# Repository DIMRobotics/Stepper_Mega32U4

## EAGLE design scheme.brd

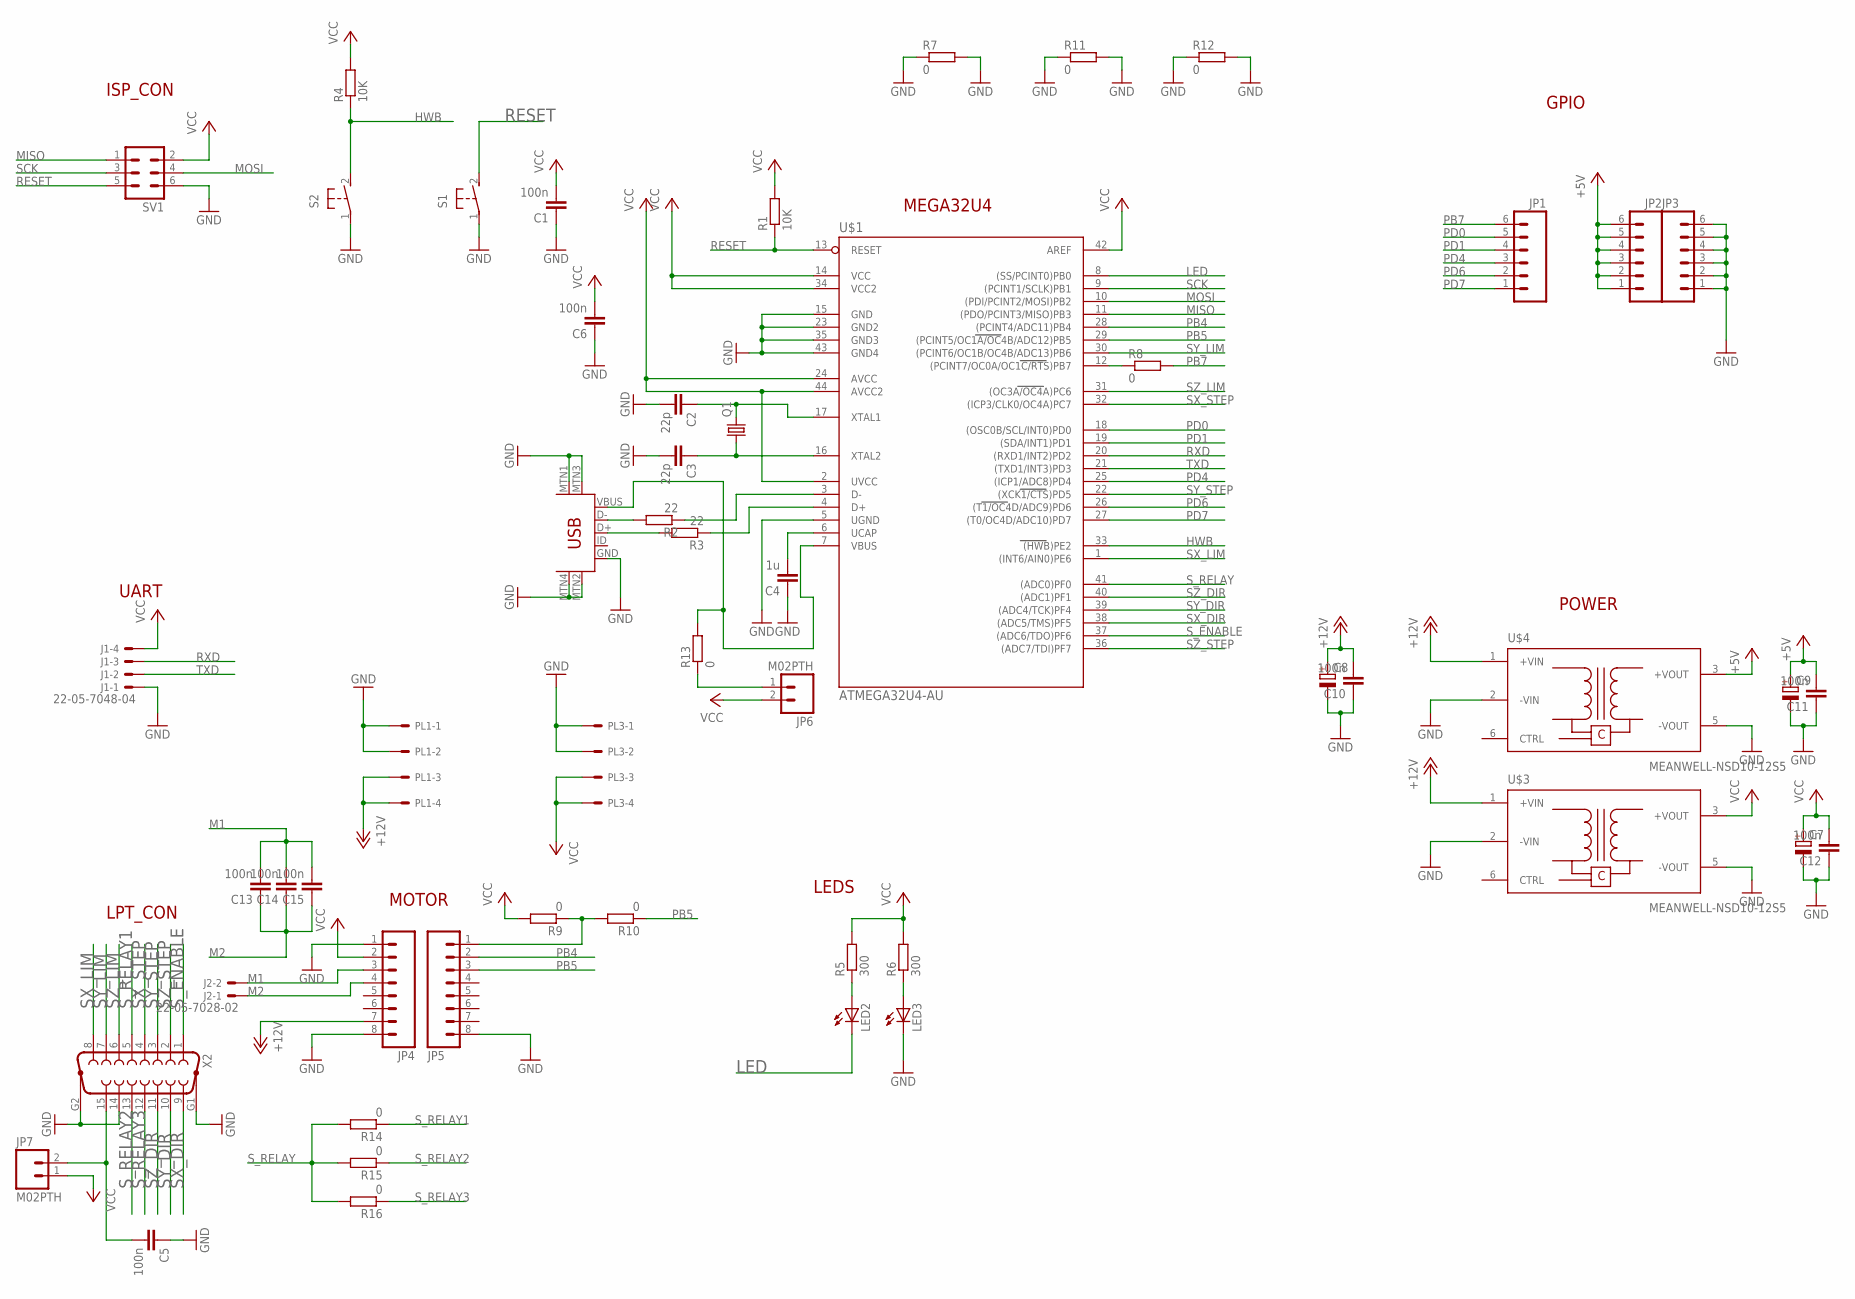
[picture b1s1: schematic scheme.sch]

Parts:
C1, C5, C6, C10, C11, C12, C13, C14, C15: 100n; C0805
C2, C3: 22p; C0805
C4: 1u; C0805
C7, C8, C9: CPOL-EUE2.5-6; E2,5-6
J1: 22-05-7048-04; 7395-04
J2: 22-05-7028-02; 7395-02
JP1, JP2, JP3: M06SIP; 1X06
JP4, JP5: M081X08; 1X08
JP6, JP7: M02PTH; 1X02
LED2, LED3: LED5MM
PL1, PL3: 555X-4H; 5569-4
Q1: CRYSTALHC49S; HC49/S
R1, R4: 10K; R0805
R2, R3: 22; R0805
R5, R6: 300; R0805
R7, R8, R11, R12, R13: 0; R1206
R9, R10, R14, R15, R16: 0; R0805
S1, S2: 31-XX; B3F-31XX
SV1: ML6L
U$1: ATMEGA32U4-AU; TQFP44
U$2: USB-MINIB-5PIN; USB-MINIB
U$3, U$4: MEANWELL-NSD10-12S5; POWER6-10W
X2: F15HP

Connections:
+5V: C9.+, C11.2, JP2.1, JP2.2, JP2.3, JP2.4, JP2.5, JP2.6, U$4.3 (+VOUT)
+12V: C8.+, C10.2, JP4.7, PL1.3, PL1.4, U$3.1 (+VIN), U$4.1 (+VIN)
GND: C1.1, C2.2, C3.2, C4.1, C5.1, C6.1, C7.-, C8.-, C9.-, C10.1, C11.1, C12.1, J1.1, JP3.1, JP3.2, JP3.3, JP3.4, JP3.5, JP3.6, JP4.1, JP4.8, JP5.8, LED3.K (C), PL1.1, PL1.2, PL3.1, PL3.2, R7.1, R7.2, R11.1, R11.2, R12.1, R12.2, S1.1, S2.1, SV1.6, U$1.5 (UGND), U$1.15 (GND), U$1.23 (GND2), U$1.35 (GND3), U$1.43 (GND4), U$2.GND, U$2.MTN1 (MTN2), U$2.MTN2 (MTN3), U$2.MTN3 (MTN1), U$2.MTN4, U$3.2 (-VIN), U$3.5 (-VOUT), U$4.2 (-VIN), U$4.5 (-VOUT), X2.14, X2.G1, X2.G2
HWB: R4.1, S2.2 (S), U$1.33 ((HWB)PE2)
LED: LED2.K (C), U$1.8 ((SS/PCINT0)PB0)
M1: C13.2, C14.2, C15.2, J2.2, JP4.3
M2: C13.1, C14.1, C15.1, J2.1, JP4.4
MISO: SV1.1, U$1.11 ((PDO/PCINT3/MISO)PB3)
MOSI: SV1.4, U$1.10 ((PDI/PCINT2/MOSI)PB2)
unnamed: C3.1, Q1.1, U$1.16 (XTAL2)
unnamed: C2.1, Q1.2, U$1.17 (XTAL1)
unnamed: LED3.A, R6.1
unnamed: R3.2, U$2.D+
unnamed: R8.1, U$1.12 ((PCINT7/OC0A/OC1C/RTS)PB7)
unnamed: R2.2, U$2.D-
unnamed: R2.1, U$1.3 (D-)
unnamed: R3.1, U$1.4 (D+)
unnamed: C4.2, U$1.6 (UCAP)
unnamed: R13.2, U$1.7 (VBUS), U$2.VBUS
unnamed: JP6.1, R13.1
unnamed: LED2.A, R5.1
unnamed: C5.2, JP7.2, X2.15
unnamed: JP5.1, R9.1, R10.2
PB4: JP5.2, U$1.28 ((PCINT4/ADC11)PB4)
PB5: JP5.3, R10.1, U$1.29 ((PCINT5/OC1A/OC4B/ADC12)PB5)
PB7: JP1.6, R8.2
PD0: JP1.5, U$1.18 ((OSC0B/SCL/INT0)PD0)
PD1: JP1.4, U$1.19 ((SDA/INT1)PD1)
PD4: JP1.3, U$1.25 ((ICP1/ADC8)PD4)
PD6: JP1.2, U$1.26 ((T1/OC4D/ADC9)PD6)
PD7: JP1.1, U$1.27 ((T0/OC4D/ADC10)PD7)
RESET: R1.1, S1.2 (S), SV1.5, U$1.13 (RESET)
RXD: J1.3, U$1.20 ((RXD1/INT2)PD2)
SCK: SV1.3, U$1.9 ((PCINT1/SCLK)PB1)
SX_DIR: U$1.38 ((ADC5/TMS)PF5), X2.9
SX_LIM: U$1.1 ((INT6/AIN0)PE6), X2.8
SX_STEP: U$1.32 ((ICP3/CLK0/OC4A)PC7), X2.4
SY_DIR: U$1.39 ((ADC4/TCK)PF4), X2.10
SY_LIM: U$1.30 ((PCINT6/OC1B/OC4B/ADC13)PB6), X2.7
SY_STEP: U$1.22 ((XCK1/CTS)PD5), X2.3
SZ_DIR: U$1.40 ((ADC1)PF1), X2.11
SZ_LIM: U$1.31 ((OC3A/OC4A)PC6), X2.6
SZ_STEP: U$1.36 ((ADC7/TDI)PF7), X2.2
S_ENABLE: U$1.37 ((ADC6/TDO)PF6), X2.1
S_RELAY: R14.2, R15.2, R16.2, U$1.41 ((ADC0)PF0)
S_RELAY1: R14.1, X2.5
S_RELAY2: R15.1, X2.13
S_RELAY3: R16.1, X2.12
TXD: J1.2, U$1.21 ((TXD1/INT3)PD3)
VCC: C1.2, C6.2, C7.+, C12.2, J1.4, JP4.2, JP6.2, JP7.1, PL3.3, PL3.4, R1.2, R4.2, R5.2, R6.2, R9.2, SV1.2, U$1.2 (UVCC), U$1.14 (VCC), U$1.24 (AVCC), U$1.34 (VCC2), U$1.42 (AREF), U$1.44 (AVCC2), U$3.3 (+VOUT)

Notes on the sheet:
ISP_CON
MEGA32U4
UART
GPIO
LPT_CON
LEDS
POWER
MOTOR

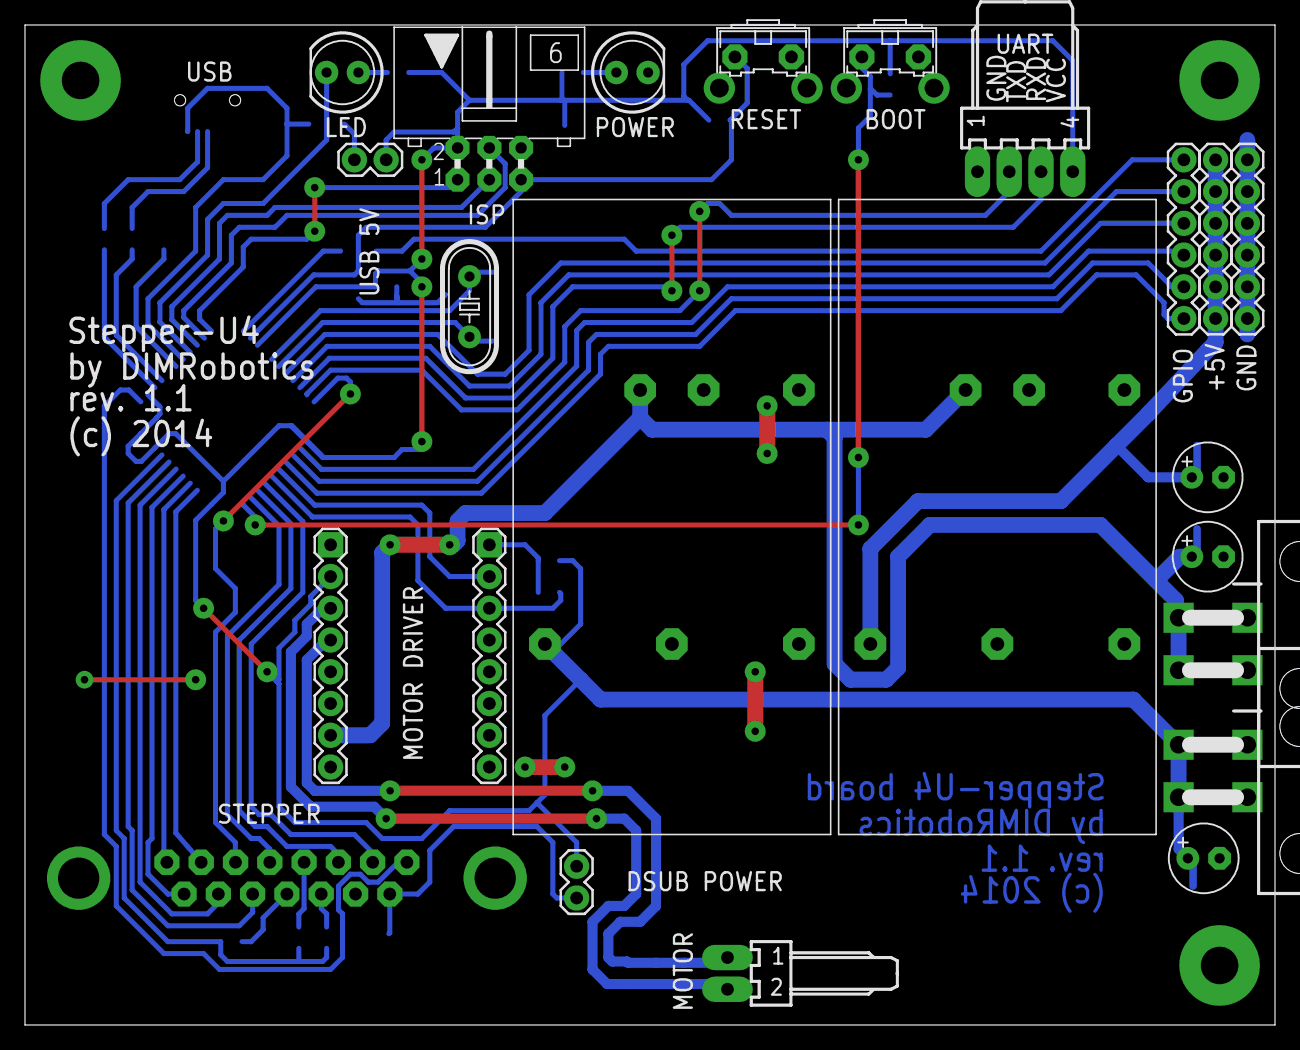
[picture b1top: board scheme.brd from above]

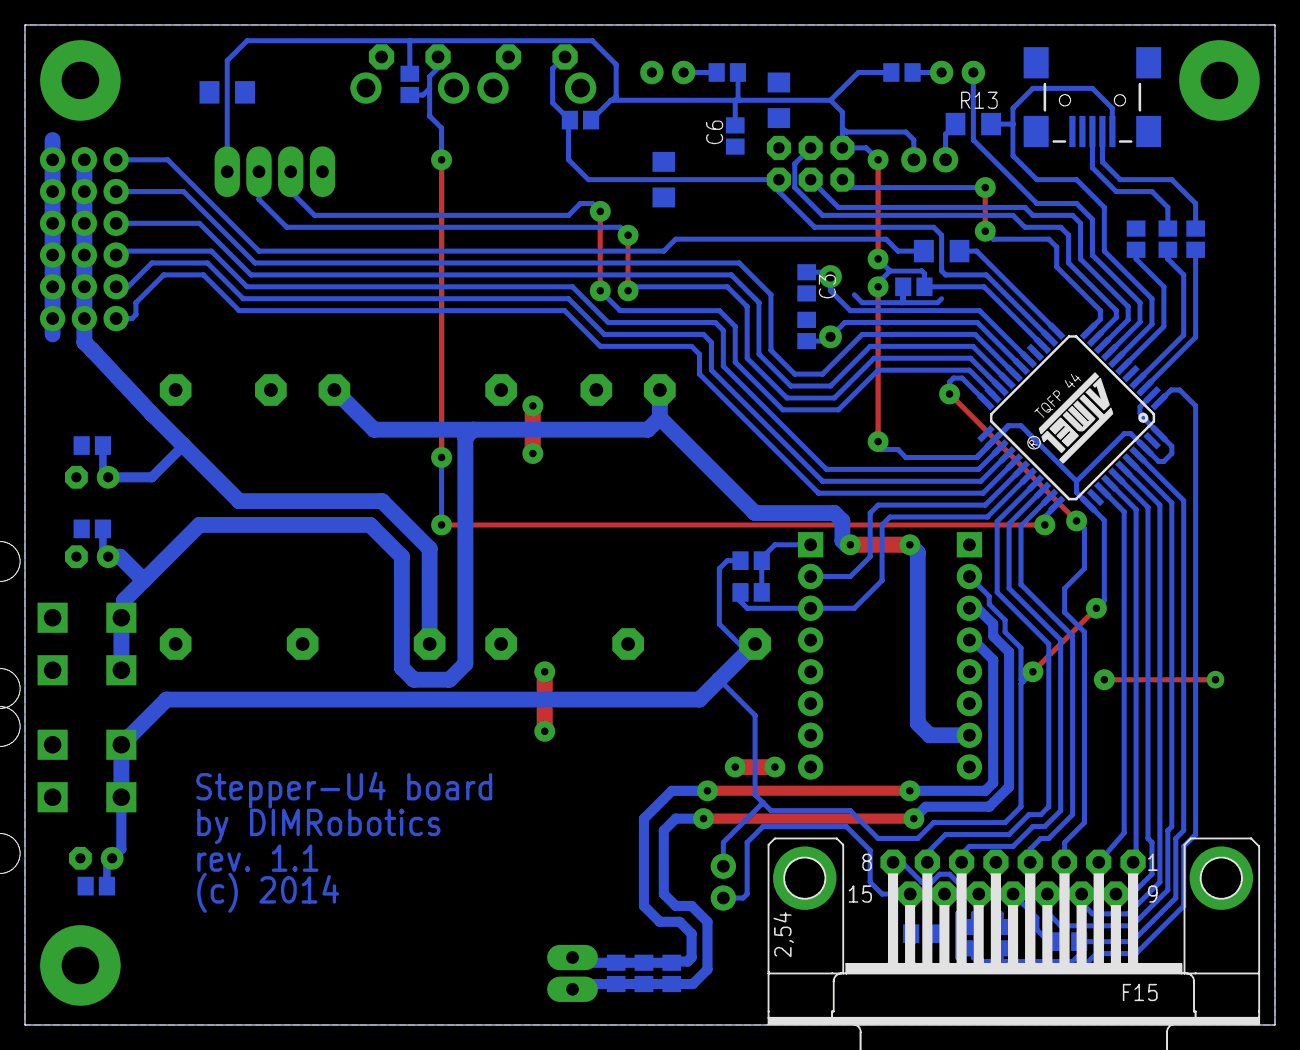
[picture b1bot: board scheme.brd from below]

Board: 2 copper layers, 100.0 x 80.0 mm, 53 parts (31 on the bottom side), 50 nets.

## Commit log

2014-01-28 Minor fix of routes
2014-02-02 Add BOOT button and fix isolation
2014-02-02 Fix jumper-wire position
2014-02-02 Reroute HWB button
2014-02-02 Add extra capacitors and rework silk
2014-02-02 Add USB power jumper
2014-02-08 Fix DB-15 connector pinout for driver
2014-02-09 Add D-SUB power jumper

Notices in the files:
scheme.brd:
(c) 2014
parts and their libraries:
SparkFun-Connectors: Licensing: CC v3.0 Share-Alike You are welcome to use this library for commercial purposes.
